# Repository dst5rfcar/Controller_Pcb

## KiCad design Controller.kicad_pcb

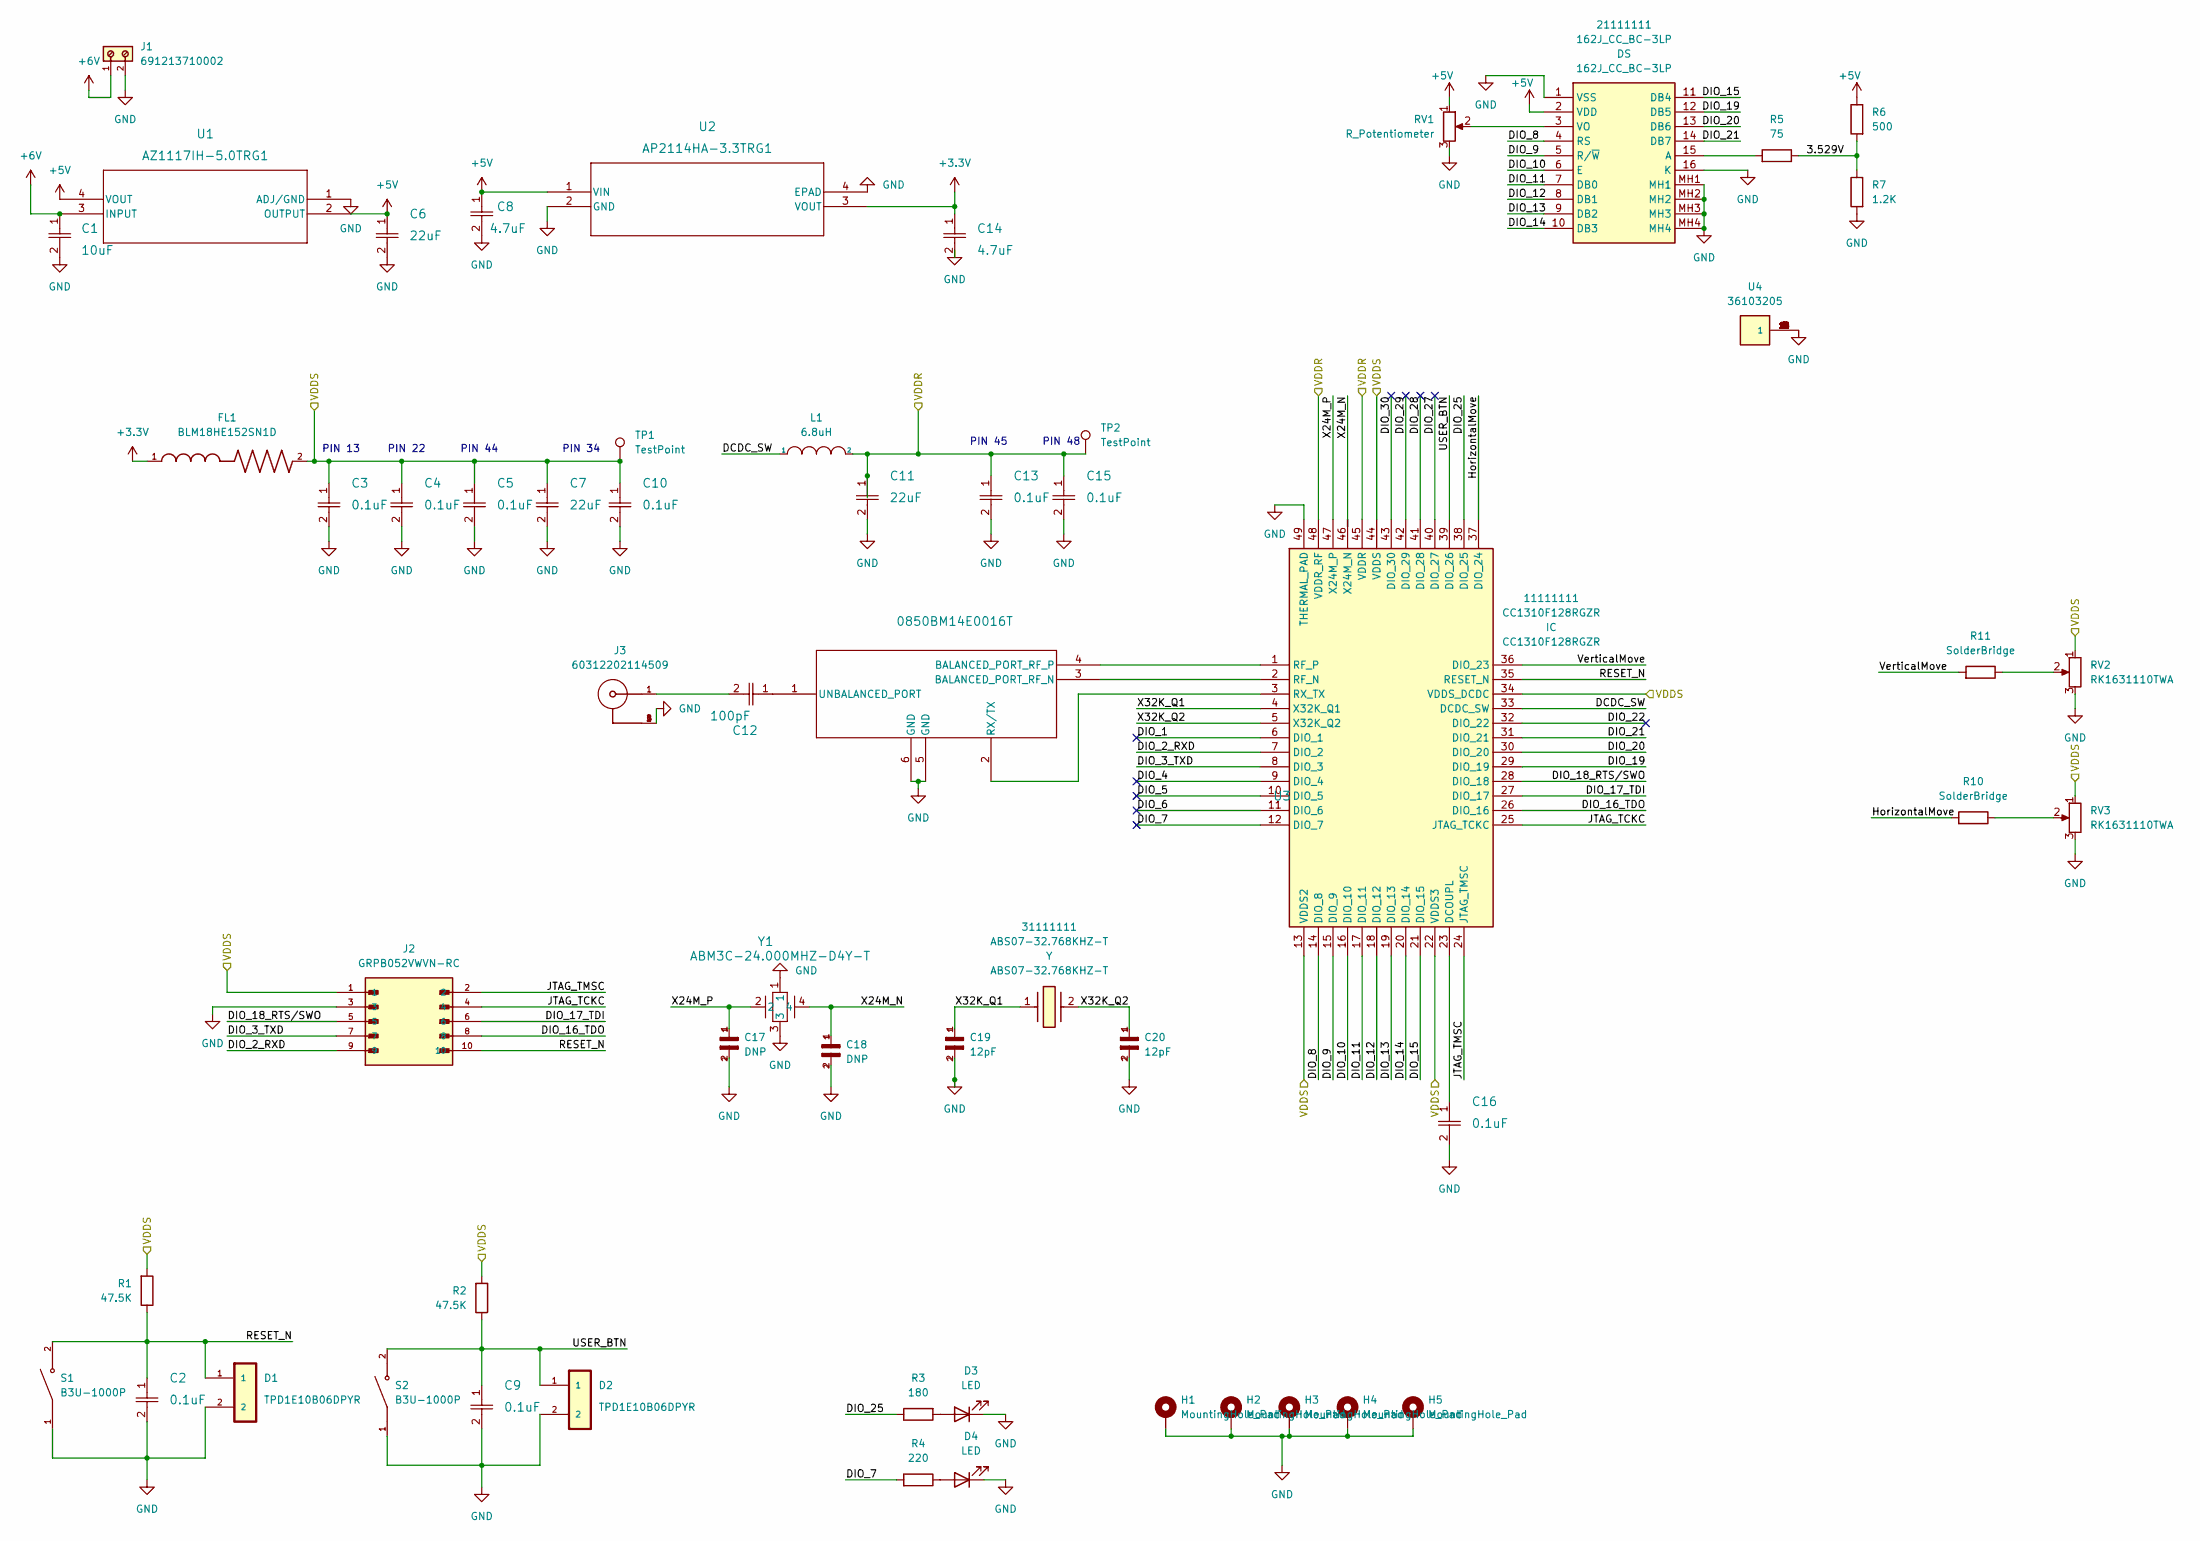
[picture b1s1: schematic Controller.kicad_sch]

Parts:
11111111: CC1310F128RGZR; QFN50P700X700X100-49N-D; Mouser Part Number 595-CC1310F128RGZR
21111111: 162J_CC_BC-3LP; 162JCCBC3LP; Mouser Part Number N/A
31111111: ABS07-32.768KHZ-T; ABS07; Mouser Part Number 815-ABS07-32.768KHZT
C1: 10uF; C_0402_1005Metric_Pad0.74x0.62mm_HandSolder
C2, C3, C4, C5, C9, C10, C13, C15, C16: 0.1uF; C_0402_1005Metric_Pad0.74x0.62mm_HandSolder
C6, C7, C11: 22uF; C_0402_1005Metric_Pad0.74x0.62mm_HandSolder
C8, C14: 4.7uF; C_0603_1608Metric_Pad1.08x0.95mm_HandSolder
C12: 100pF; C_0402_1005Metric_Pad0.74x0.62mm_HandSolder
C17, C18: DNP; C_0402_1005Metric_Pad0.74x0.62mm_HandSolder
C19, C20: 12pF; C_0402_1005Metric_Pad0.74x0.62mm_HandSolder
D1, D2: TPD1E10B06DPYR; DIO_TPD1E05U06DPYR
D3, D4: LED; LED_1206_3216Metric
FL1: BLM18HE152SN1D; BEADC1608X95N
H1, H2, H3, H4, H5: MountingHole_Pad; MountingHole_3.2mm_M3_ISO7380_Pad_TopBottom
J1: 691213710002; PART-NUMBER 691213710002
J2: GRPB052VWVN-RC; SULLINS_GRPB052VWVN-RC; PARTREV D
J3: 60312202114509; PART-NUMBER 60312202114509
L1: 6.8uH; R_0603_1608Metric_Pad0.98x0.95mm_HandSolder
R1, R2: 47.5K; R_0603_1608Metric_Pad0.98x0.95mm_HandSolder
R3: 180; R_0603_1608Metric_Pad0.98x0.95mm_HandSolder
R4: 220; R_0603_1608Metric_Pad0.98x0.95mm_HandSolder
R5: 75; R_0603_1608Metric_Pad0.98x0.95mm_HandSolder
R6: 500; R_0603_1608Metric_Pad0.98x0.95mm_HandSolder
R7: 1.2K; R_0603_1608Metric_Pad0.98x0.95mm_HandSolder
R10, R11: SolderBridge; R_0603_1608Metric_Pad0.98x0.95mm_HandSolder
RV1: R_Potentiometer; Potentiometer_Alps_RK09K_Single_Vertical
RV2, RV3: RK1631110TWA; Potentiometer_Alps_RK163_Single_Horizontal
S1, S2: B3U-1000P; SW_B3U-1000P
TP1, TP2: TestPoint; TestPoint_Pad_1.0x1.0mm
U1: AZ1117IH-5.0TRG1; SOT230P700X185-4N
U2: AP2114HA-3.3TRG1; SOT230P700X185-4N
U3: 0850BM14E0016T; 0850BM14E0016T_JOT-L
U4: 36103205; WE-SHC-SHIELDING-CABINET; MOUSER_PART_NUMBER 710-36103205
Y1: ABM3C-24.000MHZ-D4Y-T; CRYSTAL_ABM3C_ABR

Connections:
+3.3V: C14.1, FL1.1, U2.3 (VOUT)
+5V: 21111111.2 (VDD), C6.1, C8.1, R6.1, RV1.1, U1.2 (OUTPUT), U1.4 (VOUT), U2.1 (VIN)
+6V: C1.1, J1.1, U1.3 (INPUT)
/3.529V: R5.1, R6.2, R7.1
/DCDC_SW: 11111111.33 (DCDC_SW), L1.1
/DIO_1: 11111111.6 (DIO_1)
/DIO_2_RXD: 11111111.7 (DIO_2), J2.9
/DIO_3_TXD: 11111111.8 (DIO_3), J2.7
/DIO_4: 11111111.9 (DIO_4)
/DIO_5: 11111111.10 (DIO_5)
/DIO_6: 11111111.11 (DIO_6)
/DIO_7: 11111111.12 (DIO_7), R4.2
/DIO_8: 11111111.14 (DIO_8), 21111111.4 (RS)
/DIO_9: 11111111.15 (DIO_9), 21111111.5 (R/~W)
/DIO_10: 11111111.16 (DIO_10), 21111111.6 (E)
/DIO_11: 11111111.17 (DIO_11), 21111111.7 (DB0)
/DIO_12: 11111111.18 (DIO_12), 21111111.8 (DB1)
/DIO_13: 11111111.19 (DIO_13), 21111111.9 (DB2)
/DIO_14: 11111111.20 (DIO_14), 21111111.10 (DB3)
/DIO_15: 11111111.21 (DIO_15), 21111111.11 (DB4)
/DIO_16_TDO: 11111111.26 (DIO_16), J2.8
/DIO_17_TDI: 11111111.27 (DIO_17), J2.6
/DIO_18_RTS/SWO: 11111111.28 (DIO_18), J2.5
/DIO_19: 11111111.29 (DIO_19), 21111111.12 (DB5)
/DIO_20: 11111111.30 (DIO_20), 21111111.13 (DB6)
/DIO_21: 11111111.31 (DIO_21), 21111111.14 (DB7)
/DIO_22: 11111111.32 (DIO_22)
/DIO_25: 11111111.38 (DIO_25), R3.1
/DIO_27: 11111111.40 (DIO_27)
/DIO_28: 11111111.41 (DIO_28)
/DIO_29: 11111111.42 (DIO_29)
/DIO_30: 11111111.43 (DIO_30)
/HorizontalMove: 11111111.37 (DIO_24), R10.2; also elsewhere on the board
/JTAG_TCKC: 11111111.25 (JTAG_TCKC), J2.4
/JTAG_TMSC: 11111111.24 (JTAG_TMSC), J2.2
/RESET_N: 11111111.35 (RESET_N), C2.1, D1.1, J2.10, R1.1, S1.2
/USER_BTN: 11111111.39 (DIO_26), C9.1, D2.1, R2.1, S2.2
/VDDR: 11111111.45 (VDDR), 11111111.48 (VDDR_RF), C11.1, C13.1, C15.1, L1.2, TP2.1
/VDDS: 11111111.13 (VDDS2), 11111111.22 (VDDS3), 11111111.34 (VDDS_DCDC), 11111111.44 (VDDS), C3.1, C4.1, C5.1, C7.1, C10.1, FL1.2, J2.1, R1.2, R2.2, RV2.1, RV3.1, TP1.1; also elsewhere on the board
/VerticalMove: 11111111.36 (DIO_23), R11.2; also elsewhere on the board
/X24M_N: 11111111.46 (X24M_N), C18.1, Y1.4
/X24M_P: 11111111.47 (X24M_P), C17.1, Y1.2
/X32K_Q1: 11111111.4 (X32K_Q1), 31111111.1, C19.1
/X32K_Q2: 11111111.5 (X32K_Q2), 31111111.2, C20.1
GND: 11111111.49 (THERMAL_PAD), 21111111.1 (VSS), 21111111.16 (K), 21111111.MH1, 21111111.MH2, 21111111.MH3, 21111111.MH4, C1.2, C2.2, C3.2, C4.2, C5.2, C6.2, C7.2, C8.2, C9.2, C10.2, C11.2, C13.2, C14.2, C15.2, C16.2, C17.2, C18.2, C19.2, C20.2, D1.2, D2.2, D3.1 (K), D4.1 (K), H1.1, H2.1, H3.1, H4.1, H5.1, J1.2, J2.3, J3.2, J3.3, J3.4, J3.5, R7.2, RV1.3, RV2.3, RV3.3, S1.1, S2.1, U1.1 (ADJ/GND), U2.2 (GND), U2.4 (EPAD), U3.5 (GND), U3.6 (GND), U4.1, U4.2 (1), U4.3 (1), U4.4 (1), U4.5 (1), U4.6 (1), U4.7 (1), U4.8 (1), U4.9 (1), U4.10 (1), U4.11 (1), U4.12 (1), U4.13 (1), U4.14 (1), U4.15 (1), U4.16 (1), Y1.1, Y1.3; also elsewhere on the board
unnamed: 11111111.1 (RF_P), U3.4 (BALANCED_PORT_RF_P)
unnamed: 11111111.2 (RF_N), U3.3 (BALANCED_PORT_RF_N)
unnamed: 11111111.3 (RX_TX), U3.2 (RX/TX)
unnamed: 11111111.23 (DCOUPL), C16.1
unnamed: 21111111.3 (VO), RV1.2
unnamed: 21111111.15 (A), R5.2
unnamed: C12.1, U3.1 (UNBALANCED_PORT)
unnamed: C12.2, J3.1
unnamed: D3.2 (A), R3.2
unnamed: D4.2 (A), R4.1
unnamed: R10.1, RV3.2
unnamed: R11.1, RV2.2

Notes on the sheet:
PIN 22
PIN 13
PIN 48
PIN 34
PIN 45
PIN 44

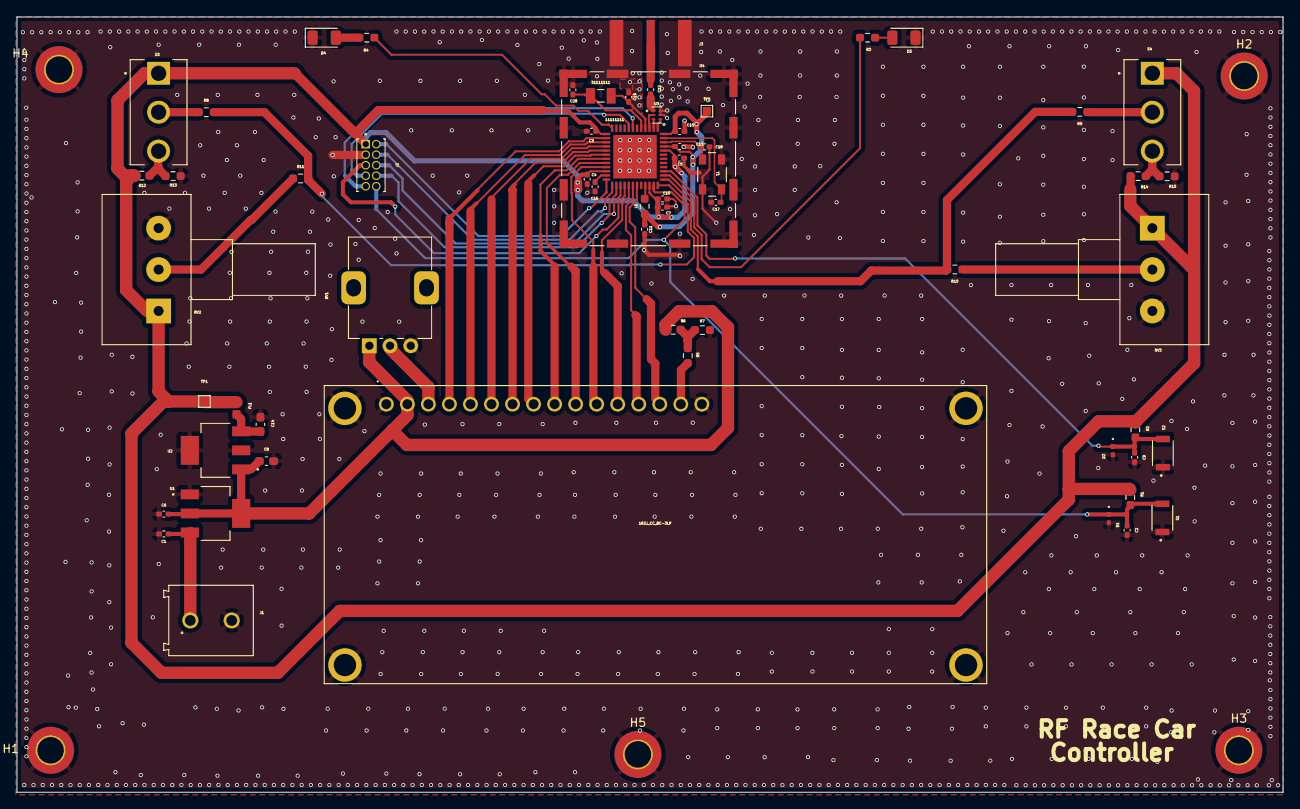
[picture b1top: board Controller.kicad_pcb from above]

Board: 2 copper layers, 152.9 x 93.6 mm, 66 parts (0 on the bottom side), 52 nets.

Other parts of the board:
R8, R9: DNP; R_0603_1608Metric_Pad0.98x0.95mm_HandSolder
R12, R13, R14, R15: 1K; R_0603_1608Metric_Pad0.98x0.95mm_HandSolder
S3, S4: 100SP1T1B4M2QE; SW_100SP1T1B4M2QE

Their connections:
/HorizontalMove: R9.2; also elsewhere on the board
/VDDS: R12.2, R14.2, S3.1, S4.1; also elsewhere on the board
/VerticalMove: R8.2; also elsewhere on the board
GND: R13.1, R15.1; also elsewhere on the board
unnamed: R8.1, S3.2
unnamed: R9.1, S4.2
unnamed: R12.1, R13.2, S3.3
unnamed: R14.1, R15.2, S4.3

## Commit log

2024-05-17 revised pcb
